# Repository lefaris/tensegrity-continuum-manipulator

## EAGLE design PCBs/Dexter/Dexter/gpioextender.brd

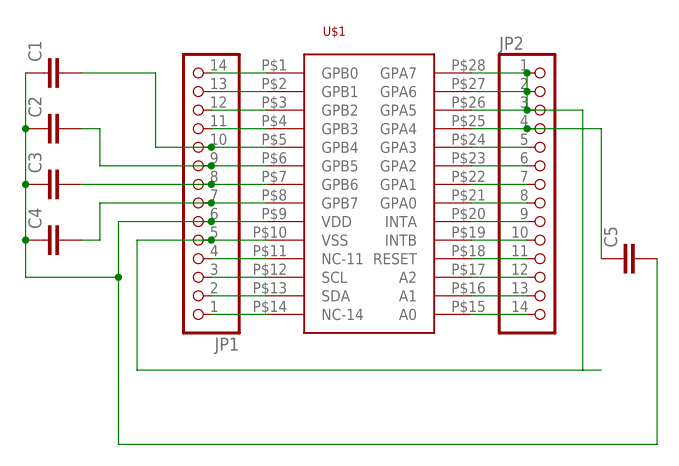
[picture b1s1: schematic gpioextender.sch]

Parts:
C1, C2, C3, C4, C5: C-EU050-025X075; C050-025X075
JP1, JP2: PINHD-1X14; 1X14
U$1: MCP23017-E/SP; DIP28

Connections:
unnamed: C1.2, C4.2, JP1.7, JP1.10, U$1.P$5 (GPB4), U$1.P$8 (GPB7)
unnamed: JP1.1, U$1.P$14 (NC-14)
unnamed: JP1.2, U$1.P$13 (SDA)
unnamed: JP1.3, U$1.P$12 (SCL)
unnamed: JP1.4, U$1.P$11 (NC-11)
unnamed: JP2.12, U$1.P$17 (A2)
unnamed: JP2.13, U$1.P$16 (A1)
unnamed: C3.2, JP1.8, U$1.P$7 (GPB6)
unnamed: C2.2, JP1.9, U$1.P$6 (GPB5)
unnamed: JP1.11, U$1.P$4 (GPB3)
unnamed: JP1.12, U$1.P$3 (GPB2)
unnamed: JP1.13, U$1.P$2 (GPB1)
unnamed: JP1.14, U$1.P$1 (GPB0)
unnamed: JP2.14, U$1.P$15 (A0)
unnamed: C1.1, C2.1, C3.1, C4.1, C5.2, JP1.6, U$1.P$9 (VDD)
unnamed: JP1.5, JP2.1, JP2.2, JP2.3, U$1.P$10 (VSS), U$1.P$26 (GPA5), U$1.P$27 (GPA6), U$1.P$28 (GPA7)
unnamed: JP2.11, U$1.P$18 (RESET)
unnamed: JP2.10, U$1.P$19 (INTB)
unnamed: JP2.9, U$1.P$20 (INTA)
unnamed: JP2.8, U$1.P$21 (GPA0)
unnamed: JP2.7, U$1.P$22 (GPA1)
unnamed: JP2.6, U$1.P$23 (GPA2)
unnamed: JP2.5, U$1.P$24 (GPA3)
unnamed: C5.1, JP2.4, U$1.P$25 (GPA4)

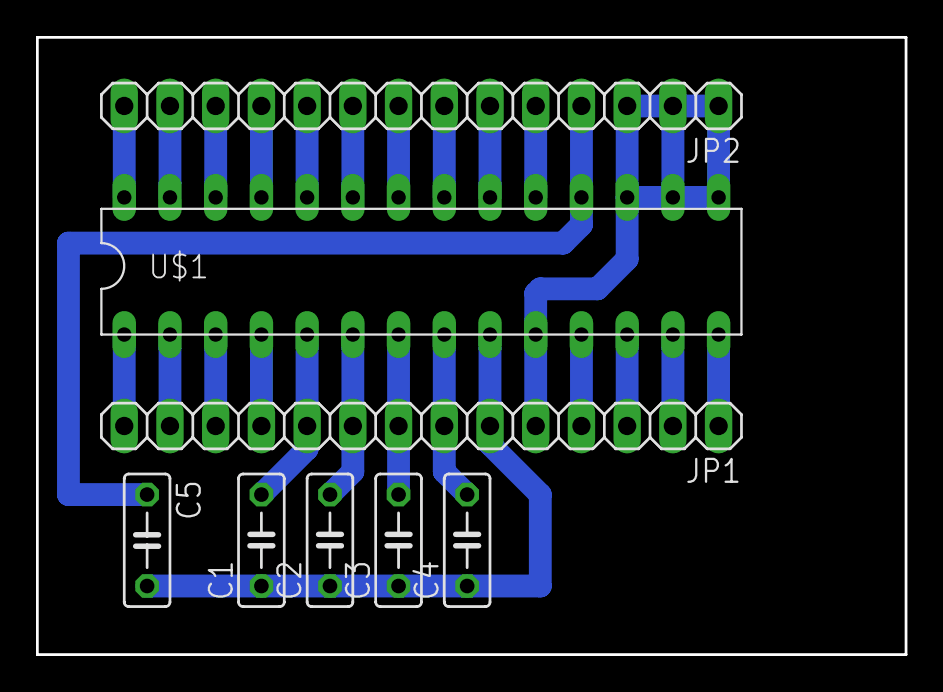
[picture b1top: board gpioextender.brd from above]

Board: 2 copper layers, 48.3 x 34.3 mm, 8 parts (0 on the bottom side), 24 nets.

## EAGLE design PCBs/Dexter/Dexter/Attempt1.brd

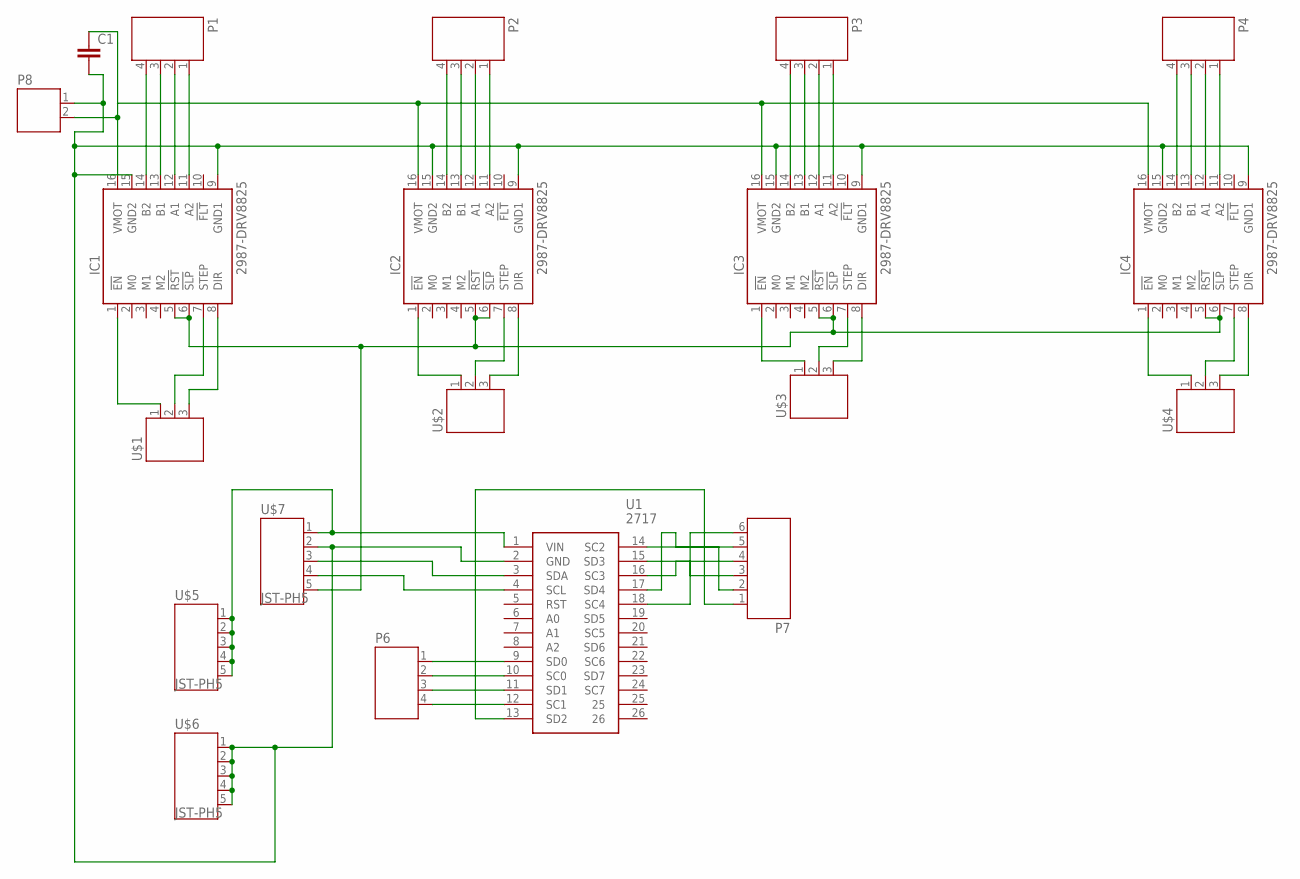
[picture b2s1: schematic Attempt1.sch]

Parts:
C1: C2.5/4; C2.5-4
IC1, IC2, IC3, IC4: 2987-DRV8825; DRV8825
P1, P2, P3, P4, P6: JST-PH4
P7: JST-PH6
P8: JST-PH2
U1: 2717
U$1, U$2, U$3, U$4: JST-PH3
U$5, U$6, U$7: JST-PH5

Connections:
unnamed: IC1.14 (B2), P1.4
unnamed: IC1.13 (B1), P1.3
unnamed: IC1.12 (A1), P1.2
unnamed: IC1.11 (A2), P1.1
unnamed: IC2.14 (B2), P2.4
unnamed: IC2.13 (B1), P2.3
unnamed: IC2.12 (A1), P2.2
unnamed: IC2.11 (A2), P2.1
unnamed: IC3.11 (A2), P3.1
unnamed: IC3.12 (A1), P3.2
unnamed: IC3.13 (B1), P3.3
unnamed: IC3.14 (B2), P3.4
unnamed: IC4.14 (B2), P4.4
unnamed: IC4.13 (B1), P4.3
unnamed: IC4.12 (A1), P4.2
unnamed: IC4.11 (A2), P4.1
unnamed: IC4.8 (DIR), U$4.3
unnamed: IC4.7 (STEP), U$4.2
unnamed: IC4.1 (!EN), U$4.1
unnamed: IC1.5 (!RST), IC1.6 (!SLP), IC2.5 (!RST), IC2.6 (!SLP), IC3.5 (!RST), IC3.6 (!SLP), IC4.5 (!RST), IC4.6 (!SLP), U$7.5
unnamed: P7.2, U1.14 (SC2)
unnamed: IC3.8 (DIR), U$3.3
unnamed: IC3.7 (STEP), U$3.2
unnamed: IC3.1 (!EN), U$3.1
unnamed: IC2.8 (DIR), U$2.3
unnamed: IC2.7 (STEP), U$2.2
unnamed: IC2.1 (!EN), U$2.1
unnamed: P7.3, U1.15 (SD3)
unnamed: C1.1, IC1.16 (VMOT), IC2.16 (VMOT), IC3.16 (VMOT), IC4.16 (VMOT), P8.2
unnamed: IC1.8 (DIR), U$1.3
unnamed: IC1.7 (STEP), U$1.2
unnamed: IC1.1 (!EN), U$1.1
unnamed: P7.4, U1.16 (SC3)
unnamed: C1.2, IC1.9 (GND1), IC1.15 (GND2), IC2.9 (GND1), IC2.15 (GND2), IC3.9 (GND1), IC3.15 (GND2), IC4.9 (GND1), IC4.15 (GND2), P8.1, U1.2 (GND), U$6.1, U$6.2, U$6.3, U$6.4, U$6.5, U$7.2
unnamed: P6.1, U1.9 (SD0)
unnamed: P6.2, U1.10 (SC0)
unnamed: P6.3, U1.11 (SD1)
unnamed: P6.4, U1.12 (SC1)
unnamed: P7.5, U1.17 (SD4)
unnamed: P7.6, U1.18 (SC4)
unnamed: P7.1, U1.13 (SD2)
unnamed: U1.3 (SDA), U$7.3
unnamed: U1.4 (SCL), U$7.4
unnamed: U1.1 (VIN), U$5.1, U$5.2, U$5.3, U$5.4, U$5.5, U$7.1

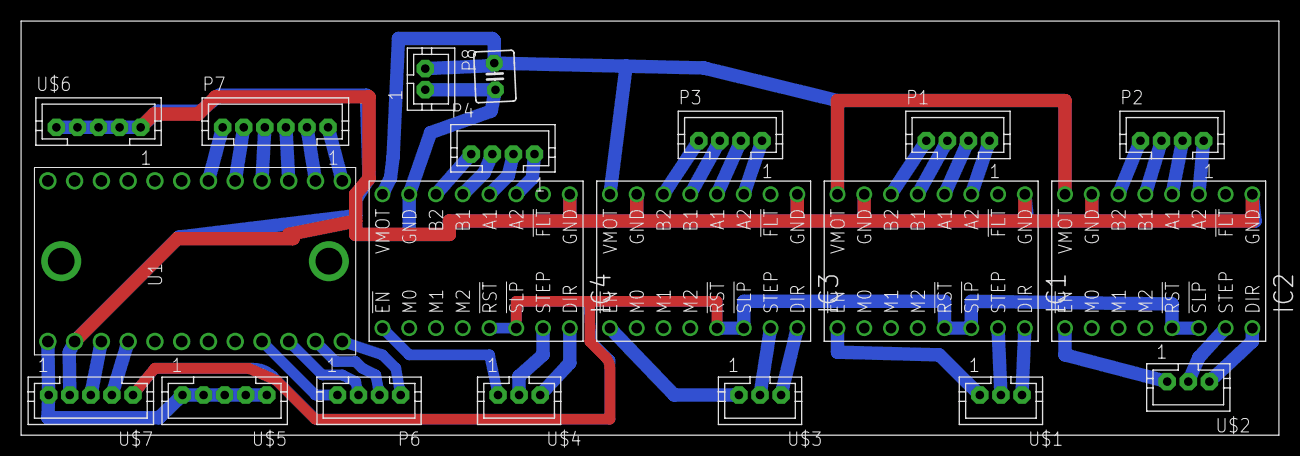
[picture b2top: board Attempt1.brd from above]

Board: 2 copper layers, 119.4 x 39.3 mm, 20 parts (0 on the bottom side), 44 nets.

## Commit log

2026-01-16 side tendon slack variable added for mod operation
2026-01-26 adding base longitudinal test script
2026-02-13 reorganized repo structure
2026-04-24 Vicon workspace data analysis
